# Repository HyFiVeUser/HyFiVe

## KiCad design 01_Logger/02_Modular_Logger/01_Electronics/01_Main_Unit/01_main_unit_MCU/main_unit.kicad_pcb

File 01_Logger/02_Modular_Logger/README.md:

# Assembly Instructions

## 1. Battery and Wi-Fi Antenna

1. Place the battery into the battery holder.
2. Attach the Wi-Fi antenna.

<table>
  <tr>
    <td></td>
    <td></td>
    <td></td>
    <td></td>
  </tr>
</table>

## 2. Measurement Sensors

Attach the measurement sensors.

## 3. Mainboard and Interface Board

1. Connect the mainboard to the interface board.
2. Ensure the correct polarity of the connector.

<table>
  <tr>
    <td></td>
    <td></td>
    <td></td>
  </tr>
</table>

## 4. Screw Components and Connect Plugs

1. Screw the parts together.
2. Plug in both NTC connectors.
3. Plug in the LED and reed switch connectors.
4. Connect the charging plug.

<table>
  <tr>
    <td></td>
    <td></td>
    <td></td>
  </tr>
</table>

## 5. LED and Reed Switch

1. Attach the LED and reed switch.
2. Secure them with hot glue.

## 6. Configure SD Card

Configure the SD card with the file `loggerConfig/logger_XX_config_2024XXXXXXXX.json`. Pay attention to the following points:

1. **Filename**: 
   - Replace "XX" in the filename with the correct logger number and date in the format year/month/day/hour/minute.
   - Example: For logger 13, the filename would be `logger_13_config_202409131028.json`

2. **Logger ID**:
   - In the configuration file, the "logger_id" field must contain the correct logger number.
   - Example: `"logger_id": "13"`

3. **Wi-Fi Setup**:
   - Configure the Wi-Fi settings.
   - The first Wi-Fi login should be for the corresponding deck box.
   - You can configure up to 5 different Wi-Fi networks.

Example for Wi-Fi configuration:

```json
"wifi": [
  {
    "ssid": "Deckbox_SSID",
    "password": "Deckbox_Password"
  },
  {
    "ssid": "Second_WiFi",
    "password": "Second_Password"
  }
]
```

## 7. Connect Battery and Start Device

1. Connect the battery voltage to the mainboard.
2. Press the Boot-BMS button.
3. The board starts and can be assembled.
4. Leak test still needs to be carried out

<table>
  <tr>
    <td></td>
    <td></td>
    <td></td>
  </tr>
</table>

## 8. Vacuum Leak Test

The following tools are required to perform the vacuum leak test:

Mityvac Hand Operated Vacuum Pump
https://bluerobotics.com/store/watertight-enclosures/enclosure-tools-supplies/vacuum-pump-kit-r2-rp/

Vacuum Plug
https://bluerobotics.com/store/watertight-enclosures/enclosure-tools-supplies/vacuum-plug/

Pressure Relief Valve Backfill Adapter
https://bluerobotics.com/store/watertight-enclosures/prv-m10-backfill-adapter/

After completing the assembly, a vacuum leak test must be performed to verify the watertight integrity of the enclosure.

1. Connect the vacuum pump to the enclosure using the appropriate adapter.

2. The target vacuum level is 30 inHg VAC (approx. 1 bar pressure differential).

3. Monitor the achieved vacuum level for approximately 24 hours.

4. If the vacuum remains stable within the permissible tolerance, the leak test is considered successful.

## 9. Battery Pack Assembly (4S3P)

The logger battery pack consists of 12 Sony/Murata US18650VTC6 cells in a 4S3P configuration.

> **Safety:** Lithium-ion cells can cause fire or serious injury if short-circuited, damaged, incorrectly connected, or overheated. Pack assembly and spot welding must only be performed by a trained person with suitable equipment and fire-safety measures.

### Materials and tools

| Qty. | Description |
|---:|---|
| 1 | Spot welder suitable for battery cells (listed peak current: at least 650 A) |
| 5 | 5-pin connector housing, Molex 43645-0500 |
| 5 | Crimp contacts, AWG 24–20, Molex 43030-0003 |
| 1 | Black hook-up wire, 1.0 mm² |
| 1 | Red hook-up wire, 1.0 mm² |
| 3 | Blue hook-up wire, 0.25 mm² |
| 2 | 10 kΩ NTC thermistors, 103AT-2 |
| 1 | Heat-shrink tubing, Ø95.5 mm × 1 m, 2:1 shrink ratio |
| 1 | Nickel strip, 0.15 mm × 10 m |
| 12 | Li-ion cells, US18650VTC6 |

### Assembly

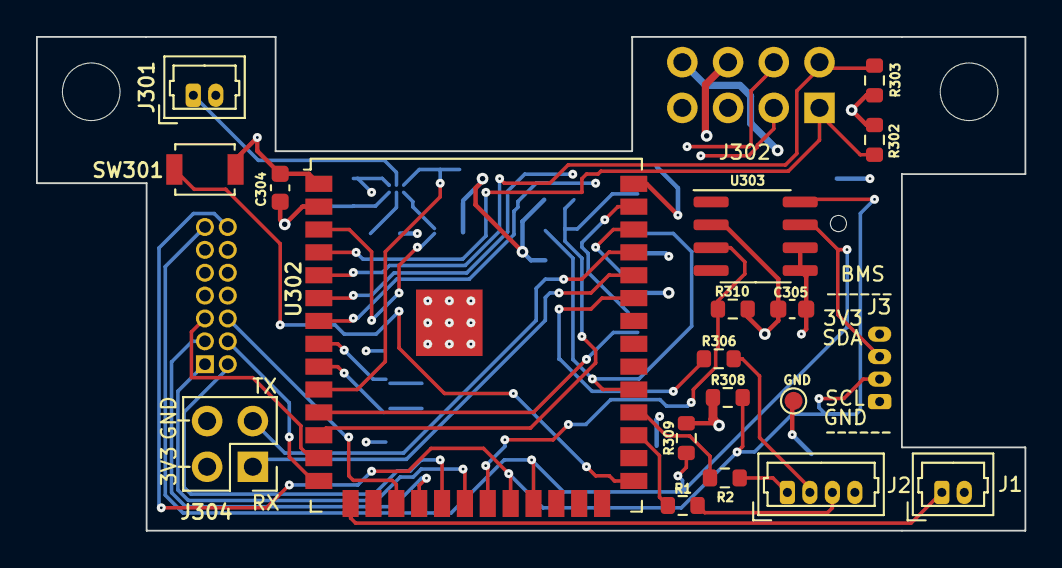
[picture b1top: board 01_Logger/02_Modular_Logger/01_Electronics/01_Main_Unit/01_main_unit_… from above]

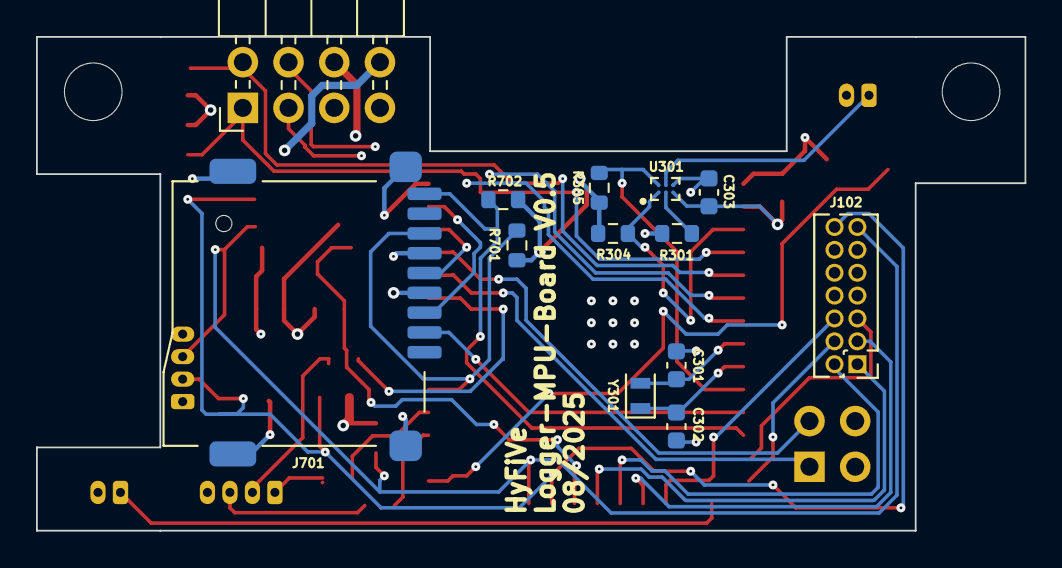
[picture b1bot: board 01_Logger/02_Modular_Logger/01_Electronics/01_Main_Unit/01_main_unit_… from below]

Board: 4 copper layers, 54.9 x 27.4 mm, 34 parts (13 on the bottom side), 35 nets.

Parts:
C301, C302: 20pF; C_0603_1608Metric
C303, C304, C305: 100nF 50V; C_0603_1608Metric
H303, H305: MountingHole; MountingHole_3.2mm_M3_ISO7380
J1, J301: Conn_01x02; Molex_PicoBlade_53047-0210_1x02_P1.25mm_Vertical
J2, J3: Conn_01x04_Pin; Molex_PicoBlade_53047-0410_1x04_P1.25mm_Vertical
J102: FTS-107-01-F-D; PinHeader_2x07_P1.27mm_Vertical
J302: Conn_02x04_Counter_Clockwise; PinHeader_2x04_P2.54mm_Horizontal
J304: Conn_02x02_Odd_Even; PinHeader_2x02_P2.54mm_Vertical
J701: Micro_SD_Card_Det; SD_CARD_693071020811
R1, R2: 0R; R_0603_1608Metric
R301: 470k; R_0603_1608Metric
R302, R303, R304, R305, R308, R309, R310, R701, R702: 10k; R_0603_1608Metric
R306: 68R; R_0603_1608Metric
SW301: SW_Push; SW_SPST_B3U-1000P
TP303: TestPoint; TestPoint_Pad_D1.0mm
U301: MAX16125WTEG00+T; WLP-6
U302: ESP32-S3-WROOM-1U
U303: DS3231MZ; SOIC-8_3.9x4.9mm_P1.27mm
Y301: Crystal; Crystal_SMD_TXC_9HT11-2Pin_2.0x1.2mm

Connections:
+3V3: C303.1, C304.1, C305.1, J3.4, J102.10, J302.8, J304.2, J701.4 (VDD), R302.1, R303.1, R304.1, R305.1, R308.1, R309.1, R310.1, R701.2, R702.1, U301.C1 (VCC), U302.2 (VDD), U303.2 (VCC)
+5V: J102.11, J302.7
+12V: J102.12, J302.6
/MPU/Charge_Enable: J102.3, U302.18 (IO10)
/MPU/ENABLE_5V: J102.1, U302.20 (IO12)
/MPU/ENABLE_12V: J102.2, U302.19 (IO11)
/MPU/GPIO_Reserve_B2B: J302.4, U302.6 (IO6)
/MPU/I2C_BUS_CLK: J302.2, R303.2, U302.5 (IO5)
/MPU/I2C_BUS_SDA: J302.1, R302.2, U302.4 (IO4)
/MPU/I2C_SMBus_SCL: J3.2, J102.14, R308.2, U302.22 (IO14), U303.8 (SCL)
/MPU/I2C_SMBus_SDA: J3.3, J102.13, R309.2, U302.23 (IO21), U303.7 (SDA)
/MPU/Interface_RST: J302.3, U302.7 (IO7)
/MPU/LED_ROT: R306.1, U302.35 (IO42)
/MPU/RST: R304.2, U301.A1 (/RESET), U302.3 (EN)
/MPU/RTC_INTERRUPT: R310.2, U302.21 (IO13), U303.3 (~INT/SQW)
/MPU/SD_CARD_DETECT: J701.9 (DET_B), R702.2, U302.12 (IO8)
/MPU/SD_V_SPI_CLK: J701.5 (CLK), U302.38 (IO2)
/MPU/SD_V_SPI_CS: J701.2 (DAT3/CD), U302.11 (IO18)
/MPU/SD_V_SPI_MISO: J701.7 (DAT0), R701.1, U302.31 (IO38)
/MPU/SD_V_SPI_MOSI: J701.3 (CMD), U302.39 (IO1)
/MPU/UART_RXD0: J304.1, U302.36 (RXD0)
/MPU/UART_TXD0: J304.3, U302.37 (TXD0)
/MPU/~PG: J102.4, U302.14 (IO20)
/MPU/~STAT1: J102.6, U302.17 (IO9)
/MPU/~STAT2: J102.5, U302.13 (IO19)
GND: C301.2, C302.2, C303.2, C304.2, C305.2, J1.2, J2.4, J3.1, J102.7, J102.8, J301.2, J302.5, J304.4, J701.6 (VSS), J701.10 (DET_A), J701.11 (SHIELD), J701.12 (SHIELD), J701.13 (SHIELD), R301.2, SW301.2, TP303.1, U301.C2 (GND), U302.1 (GND), U302.40 (GND), U302.EPAD (GND), U303.5 (GND), U303.6 (VBAT)
unnamed: J2.1, R2.1
unnamed: J2.2, R306.2
unnamed: J2.3, R1.1
unnamed: J301.1, U301.B2 (/MR)
unnamed: R301.1, U301.B1 (SEL)
unnamed: R305.2, U301.A2 (/SRESET), U302.10 (IO17)
unnamed: SW301.1, U302.27 (IO0)
unnamed: C301.1, U302.8 (IO15), Y301.2
unnamed: C302.1, U302.9 (IO16), Y301.1

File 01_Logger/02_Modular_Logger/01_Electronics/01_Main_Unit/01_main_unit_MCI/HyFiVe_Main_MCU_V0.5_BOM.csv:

"Reference","Value","Datasheet","Footprint","Qty","DNP","eurocircuits_MPN"
"C301,C302","20pF","~","Capacitor_SMD:C_0603_1608Metric","2","","CL10C200JB8NNNC"
"C303,C304,C305","100nF 50V","~","Capacitor_SMD:C_0603_1608Metric","3","","885012206095"
"FID301,FID302,FID303,FID304","Fiducial","~","Sonstiges:Passmarke","4","",""
"H303,H305","MountingHole","~","MountingHole:MountingHole_3.2mm_M3_ISO7380","2","",""
"J1","Conn_01x02","~","Connector_Molex:Molex_PicoBlade_53047-0210_1x02_P1.25mm_Vertical","1","Nicht bestücken","53047-0210"
"J2","Conn_01x04_Pin","~","Connector_Molex:Molex_PicoBlade_53047-0410_1x04_P1.25mm_Vertical","1","","53047-0410"
"J3","Conn_01x04_Pin","~","Connector_Molex:Molex_PicoBlade_53047-0410_1x04_P1.25mm_Vertical","1","Nicht bestücken","53047-0410"
"J102","FTS-107-01-F-D","https://www.mouser.de/datasheet/2/527/fts-2854063.pdf","Connector_PinHeader_1.27mm:PinHeader_2x07_P1.27mm_Vertical","1","","FTS-107-01-F-D"
"J301","Conn_01x02","~","Connector_Molex:Molex_PicoBlade_53047-0210_1x02_P1.25mm_Vertical","1","","53047-0210"
"J302","Conn_02x04_Counter_Clockwise","~","Connector_PinHeader_2.54mm:PinHeader_2x04_P2.54mm_Horizontal","1","Nicht bestücken",""
"J304","Conn_02x02_Odd_Even","~","Connector_PinHeader_2.54mm:PinHeader_2x02_P2.54mm_Vertical","1","","61300421121"
"J701","Micro_SD_Card_Det","https://www.hirose.com/product/en/download_file/key_name/DM3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","HER_Footprints:SD_CARD_693071020811","1","","693071020811"
"R1,R2","0R","~","Resistor_SMD:R_0603_1608Metric","2","","GPR06030R"
"R301","470k","~","Resistor_SMD:R_0603_1608Metric","1","","GPR0603470K"
"R302,R303,R304,R305,R308,R309,R310,R701,R702","10k","~","Resistor_SMD:R_0603_1608Metric","9","","MCWR06X1002FTL"
"R306","68R","~","Resistor_SMD:R_0603_1608Metric","1","","GPR060368R"
"SW301","SW_Push","~","Button_Switch_SMD:SW_SPST_B3U-1000P","1","","B3U-1000P"
"TP303","TestPoint","~","TestPoint:TestPoint_Pad_D1.0mm","1","",""
"U301","MAX16125WTEG00+T","","MAX6071ANT25_T:WLP-6","1","","MAX16125WTEG00+T"
"U302","ESP32-S3-WROOM-1U","https://www.espressif.com/sites/default/files/documentation/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","HER_Footprints:ESP32-S3-WROOM-1U","1","","ESP32-S3-WROOM-1U-N16R8"
"U303","DS3231MZ","http://datasheets.maximintegrated.com/en/ds/DS3231M.pdf","Package_SO:SOIC-8_3.9x4.9mm_P1.27mm","1","","DS3231MZ+"
"Y301","Crystal","~","Crystal:Crystal_SMD_TXC_9HT11-2Pin_2.0x1.2mm","1","","9HT11-32.768KDZF-T "

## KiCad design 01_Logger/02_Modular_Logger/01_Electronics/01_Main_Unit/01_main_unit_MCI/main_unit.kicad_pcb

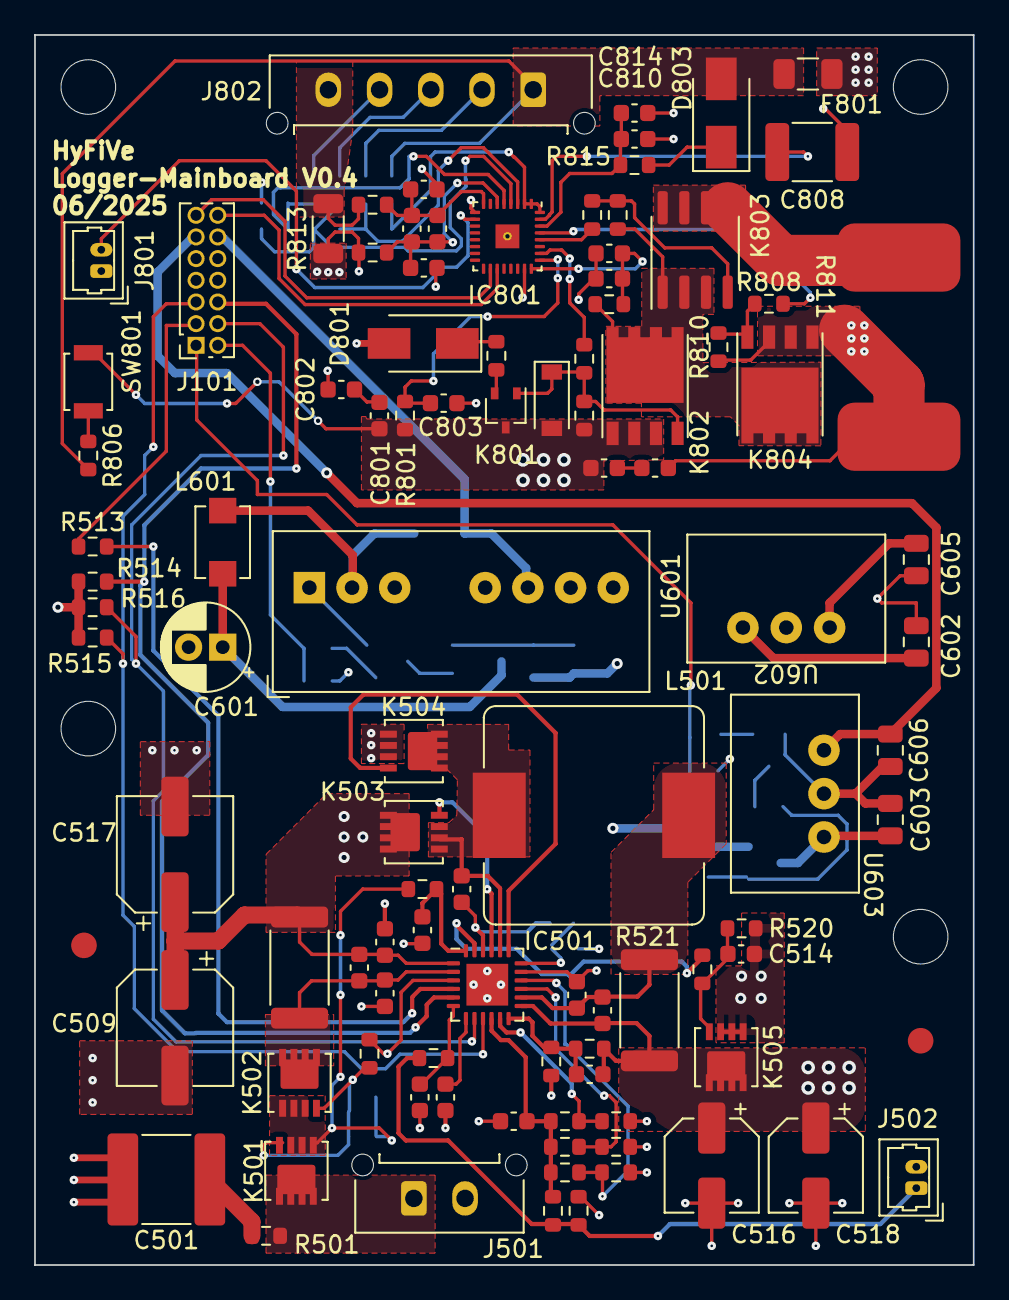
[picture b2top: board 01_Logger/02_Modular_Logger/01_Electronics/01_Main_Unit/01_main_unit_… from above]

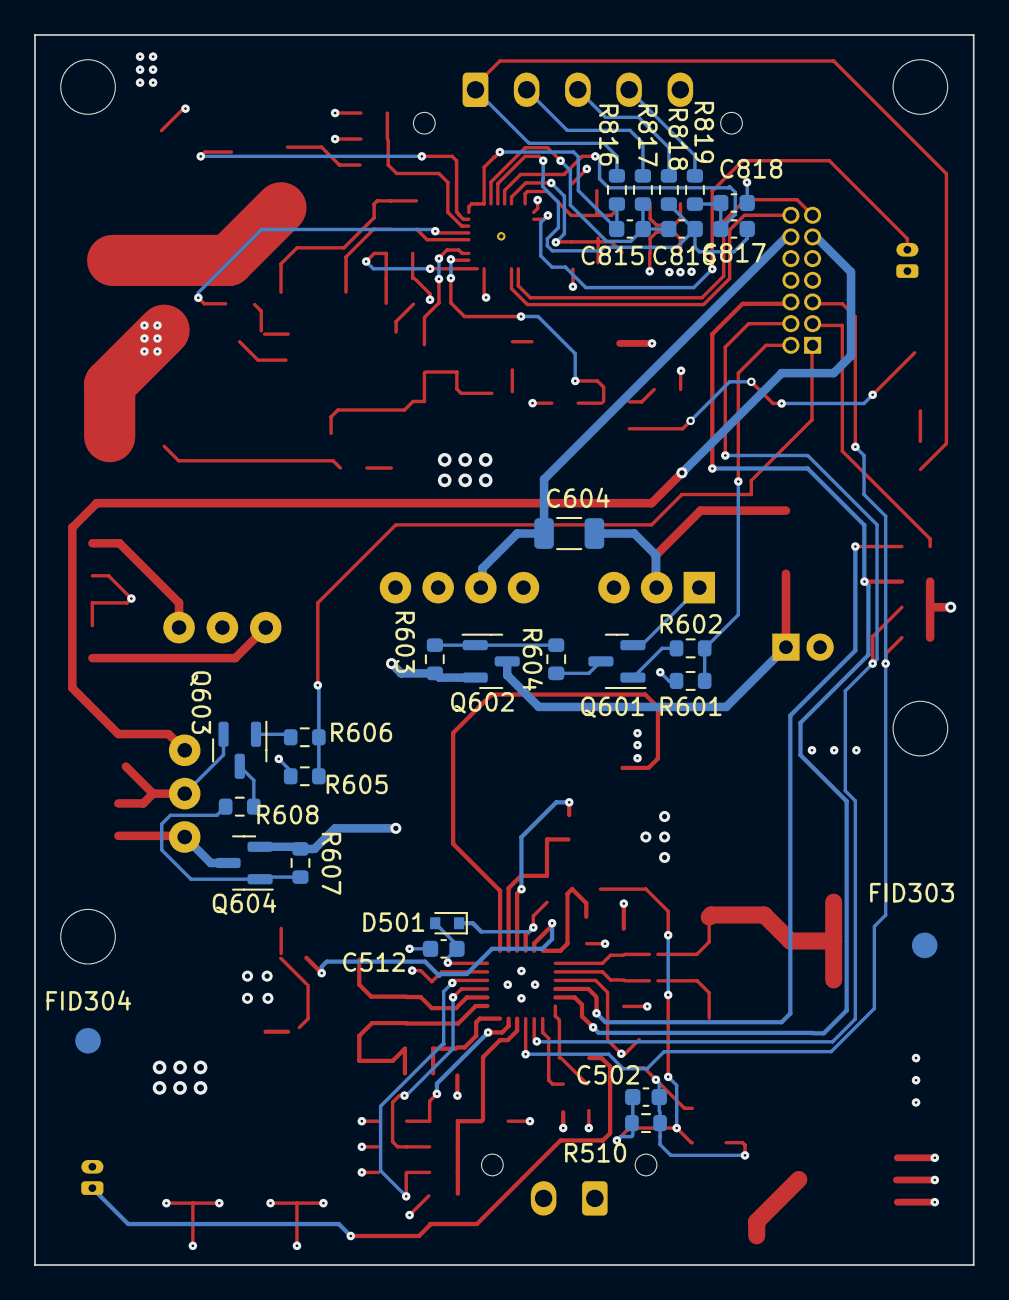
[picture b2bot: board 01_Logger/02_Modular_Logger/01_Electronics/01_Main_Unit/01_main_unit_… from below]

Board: 4 copper layers, 55.0 x 72.1 mm, 132 parts (27 on the bottom side), 78 nets.

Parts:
C501: 47µF 35V X7R; C_2220_5650Metric
C502, C503, C505, C506, C507, C511, C513, C514, C515, C801, C802, C806, C807, C809, C812, C813, C815, C816, C817, C818: 100nF 50V; C_0603_1608Metric
C504: 1µF 10V; C_0603_1608Metric
C508: 33nF 25V; C_0603_1608Metric
C509, C517: 47µF 35V; CP_Elec_6.3x5.4
C510, C512: 1µF 35V; C_0603_1608Metric
C516, C518: 20µF 35V; CP_Elec_5x5.3
C519: 22pF 35V; C_0603_1608Metric
C601: 10µF, 50V; CP_Radial_D5.0mm_P2.00mm
C602, C603: 22µF 30V; C_0805_2012Metric
C604: 150pF, 2kV; C_1206_3216Metric
C605, C606: 47µF 10V; C_0805_2012Metric
C803: 10nF, 50V; C_0603_1608Metric
C804, C805, C810, C814: 100pF 50V; C_0603_1608Metric
C808: 2,2µF 100V; C_1812_4532Metric
C811: 100pF 100V; C_0603_1608Metric
D501: BAT54W; D_SOD-523
D801, D803: SS1H10-E3/61T; D_SMA
D802: MMSZ5246B-7-F; D_SOD-123
F801: 12A; Fuse_1206_3216Metric
FID301, FID302, FID303, FID304: Fiducial; Passmarke
H301, H302, H304, H306: MountingHole; MountingHole_3.2mm_M3_ISO7380
IC501: BQ24618; VQFN-24-1EP_4x4mm_P0.5mm_EP2.45x2.45mm
IC801: BQ40Z80; RSM32 VQFN-32-1EP_4x4mm_P0.4mm_EP1.4x1.4mm_ThermalVias
J101: SFMC-107-01-L-D; PinSocket_2x07_P1.27mm_Vertical
J501: Conn_01x02; Molex_Micro-Fit_3.0_43650-0215_1x02_P3.00mm_Vertical
J502: Conn_01x02_Female; Molex_PicoBlade_53047-0210_1x02_P1.25mm_Vertical
J801: Conn_01x02_Male; Molex_PicoBlade_53047-0210_1x02_P1.25mm_Vertical
J802: Conn_01x05_Male; Molex_Micro-Fit_3.0_43650-0515_1x05_P3.00mm_Vertical
K501, K502, K505: SISH101DN-T1-GE3; PowerPAK 1212-8 Single
K503, K504: SiS412DN; PowerPAK 1212-8 Single
K801: 2N7002KW; SOT-323_SC-70
K802, K804: CSD18540Q5B; TI Q5B-Package
K803: DMP6023LSS-13; SOIC-8_3.9x4.9mm_P1.27mm
L501: 3,3µH; L_Bourns_SRP1245A
L601: 10µH; CC453232A
Q601, Q603: BSS123; SOT-23
Q602, Q604: IRLML5203TRPBF; SOT-23
R501, R511, R812, R814, R815: 100R; R_0603_1608Metric
R502, R507, R802, R809: 10k; R_0603_1608Metric
R503: 5.7k; R_0603_1608Metric
R504: R_Therm_1; R_0603_1608Metric
R505: R_Therm_2; R_0603_1608Metric
R506, R510, R520: 100k; R_0603_1608Metric
R508: 232k; R_0603_1608Metric
R509: 33k; R_0603_1608Metric
R512, R519, R604, R608, R808: 1k; R_0603_1608Metric
R513: 0R; R_0603_1608Metric
R514, R515, R516, R523: 49,9k; R_0603_1608Metric
R517, R521: 10m; R_2512_6332Metric
R518: 10R; R_0603_1608Metric
R522: 357k; R_0603_1608Metric
R601, R605: 2k7; R_0603_1608Metric
R602, R606: 47k; R_0603_1608Metric
R603, R607: 680k; R_0603_1608Metric
R801: 1,1k; R_0603_1608Metric
R803, R807, R810: 10M; R_0603_1608Metric
R804: 4,81k; R_0603_1608Metric
R805: 510R; R_0603_1608Metric
R806: 51R; R_0603_1608Metric
R811: 46.4 5W; R_4527_11570Metric
R813: 1m; R_1206_3216Metric
R816, R817, R818, R819: 499R; R_0603_1608Metric
SW801: SW_Push; SW_SPST_B3U-1000P
U601: SPBW06F-12; Converter_DCDC_XP_POWER-ITxxxxxS_THT
U602: OKI-78SR-3.3_1.5-W36-C; DC_DC_Converter
U603: OKI-78SR-5_1.5-W36-C; DC_DC_Converter

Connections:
+3V3: C605.1, J101.10, R514.1, R515.1, R516.1, U602.3 (OUT)
+5V: C606.1, J101.11, U603.3 (OUT)
+12V: C604.2, J101.12, U601.6 (+VOUT)
/power/BMS/BAT_MINUS: J802.5, R813.2, R814.1
/power/BMS/BAT_PLUS: D803.2 (A), F801.2, J802.1, R806.2, R816.1
/power/BMS/BAT_PLUS_F: C807.1, F801.1, K804.1, K804.2, K804.3, R810.2, R811.2
/power/BMS/PACK+: C515.1, C516.1, C518.1, C519.2, C801.1, C806.1, D802.2 (A), IC501.13 (SRN), K505.5, K505.6, K505.7, K505.8, K505.9, K801.3, K802.1, K802.2, K802.3, R521.1, R522.1, R801.2, R803.2, SW801.2
/power/Battery_Charger/ACP: C503.2, C505.1, IC501.2 (ACP), K502.5, K502.6, K502.7, K502.8, K502.9, R517.2
/power/Battery_Charger/Thermistor: J502.1, R504.1, R505.2, R511.1
/power/Battery_Charger/VIN: J501.1, K501.5, K501.6, K501.7, K501.8, K501.9, R501.1
/power/Battery_Charger/VREF: C504.1, IC501.10 (VREF), R502.1, R504.2, R506.1, R508.1
/power/Charge_Enable: J101.3, R513.1
/power/ENABLE_5V: J101.1, R605.2, R606.1
/power/ENABLE_12V: J101.2, R601.2, R602.1
/power/I2C_SMBus_SCL: IC801.19 (SMBC), J101.14
/power/I2C_SMBus_SDA: IC801.18 (SMBD), J101.13
/power/System+: C505.2, C507.2, C509.1, C514.1, C517.1, C602.1, IC501.1 (ACN), K503.5, K503.6, K503.7, K503.8, K503.9, K505.1, K505.2 (S), K505.3 (S), Q602.2 (S), Q604.2 (S), R517.1, R520.1, R603.2, R607.2, U602.1 (IN)
/power/~PG: IC501.8 (~PG), J101.4, R516.2
/power/~STAT1: IC501.5 (~STAT1), J101.6, R514.2
/power/~STAT2: IC501.9 (~STAT2), J101.5, R515.2
GND: C501.2, C503.1, C504.2, C506.1, C507.1, C508.1, C509.2, C510.2, C512.2, C513.1, C516.2, C517.2, C518.2, C601.2, C602.2, C603.2, C605.2, C606.2, C802.2, C803.2, C804.1, C805.1, C808.2, C809.1, C810.1, C813.1, C814.1, C818.2, D801.2 (A), IC501.17 (GND), IC501.25 (PwrPad), IC801.9 (VSS), IC801.23 (FUSE), IC801.33 (PAD), J101.7, J101.8, J501.2, J502.2, J801.1, K504.1, K504.2 (S), K504.3 (S), Q601.2 (S), Q603.2 (S), R503.2, R505.1, R507.2, R509.2, R523.2, R601.1, R605.1, R812.2, R813.1, U601.1 (-VIN), U601.7 (-VOUT), U602.2 (GND), U603.2 (GND)
unnamed: C501.1, R501.2
unnamed: C502.1, K501.1, K501.2 (S), K501.3 (S), K502.1, K502.2 (S), K502.3 (S), R510.1, R518.2
unnamed: C502.2, K501.4, K502.4, R510.2, R512.1
unnamed: C514.2, K505.4, R519.1, R520.2
unnamed: C801.2, C802.1
unnamed: C806.2, C807.2
unnamed: C512.1, D501.2 (A), IC501.18 (REGN)
unnamed: C511.1, D501.1 (K), IC501.22 (BTST)
unnamed: D801.1 (K), R802.1
unnamed: D802.1 (K), K801.1, K802.4, R803.1, R804.2
unnamed: D803.1 (K), R815.1
unnamed: IC501.16 (ACSET), R502.2, R503.1
unnamed: IC501.4 (CE), R513.2
unnamed: IC501.21 (HIDRV), K503.4
unnamed: IC501.11 (ISET1), R508.2, R509.1
unnamed: IC501.15 (ISET2), R506.2, R507.1
unnamed: IC501.19 (LODRV), K504.4
unnamed: C511.2, IC501.20 (PH), K503.1, K503.2 (S), K503.3 (S), K504.5, K504.6, K504.7, K504.8, K504.9, L501.1
unnamed: C513.2, C515.2, IC501.14 (SRP), L501.2, R521.2
unnamed: C506.2, IC501.6 (TS), R511.2
unnamed: C508.2, IC501.7 (TTC)
unnamed: C510.1, IC501.24 (VCC), R518.1
unnamed: C519.1, IC501.12 (VFB), R522.2, R523.1
unnamed: IC501.3 (~ACDRV), R512.2
unnamed: IC501.23 (~BATDRV), R519.2
unnamed: C810.2, C814.2, IC801.30 (BAT), R815.2
unnamed: IC801.29 (CHG), R808.1
unnamed: IC801.26 (DSG), R804.1
unnamed: C808.1, IC801.31 (PBI)
unnamed: IC801.28 (PCHG), R809.1
unnamed: C803.1, IC801.25 (Pack), R801.1
unnamed: C809.2, C811.2, C812.2, IC801.6 (SRN), R812.1
unnamed: C811.1, C812.1, C813.2, IC801.8 (SRP), R814.2
unnamed: IC801.10 (TS1), J801.2
unnamed: C817.2, C818.1, IC801.5 (VC1), R819.2
unnamed: C816.2, C817.1, IC801.4 (VC2), R818.2
unnamed: C815.2, C816.1, IC801.3 (VC3), R817.2
unnamed: C815.1, IC801.1 (VC5), IC801.2 (VC4), IC801.32 (VC6), R816.2
unnamed: C804.2, C805.2, IC801.24 (VCC), R805.1
unnamed: J802.2, R817.1
unnamed: J802.3, R818.1
unnamed: J802.4, R819.1
unnamed: K801.2, R802.2
unnamed: K802.5, K802.6, K802.7, K802.8, K802.9, K803.1, K803.2, K803.3, K804.5, K804.6, K804.7, K804.8, K804.9, R805.2, R807.2
unnamed: K803.4, R807.1, R809.2
unnamed: K803.5, K803.6, K803.7, K803.8, R811.1
unnamed: K804.4, R808.2, R810.1
unnamed: Q601.3 (D), R604.1
unnamed: Q601.1 (G), R602.2
unnamed: C601.1, L601.1, Q602.3 (D)
unnamed: Q602.1 (G), R603.1, R604.2
unnamed: Q603.3 (D), R608.1
unnamed: Q603.1 (G), R606.2
unnamed: C603.1, Q604.3 (D), U603.1 (IN)
unnamed: Q604.1 (G), R607.1, R608.2
unnamed: R806.1, SW801.1
unnamed: C604.1, L601.2, U601.2 (+VIN)

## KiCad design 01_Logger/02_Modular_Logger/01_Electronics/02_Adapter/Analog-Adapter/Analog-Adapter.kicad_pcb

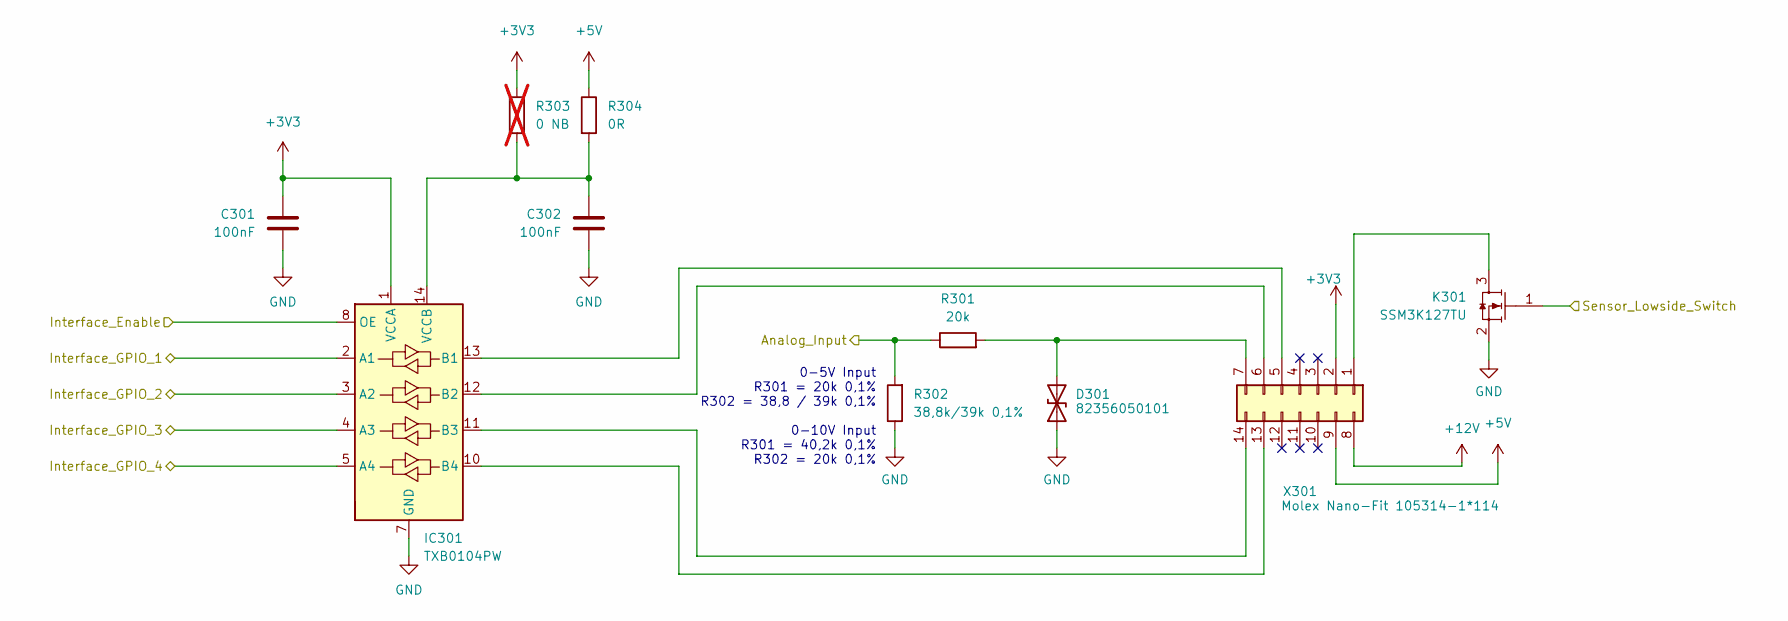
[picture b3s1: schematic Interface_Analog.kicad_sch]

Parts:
C301, C302: 100nF; C_0603_1608Metric_Pad1.08x0.95mm_HandSolder
D301: 82356050101; D_0603_1608Metric
IC301: TXB0104PW; TSSOP-14_4.4x5mm_P0.65mm
K301: SSM3K127TU; SOT-23
R301: 20k; R_0603_1608Metric_Pad0.98x0.95mm_HandSolder
R302: 38,8k/39k 0,1%; R_0603_1608Metric_Pad0.98x0.95mm_HandSolder
R303: 0 NB; R_0603_1608Metric_Pad0.98x0.95mm_HandSolder; not fitted
R304: 0R; R_0603_1608Metric_Pad0.98x0.95mm_HandSolder
X301: Molex Nano-Fit 105314-1*114; Molex_Nano-Fit_105314-xx14_2x07_P2.50mm_Horizontal

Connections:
+3V3: C301.1, IC301.1 (VCCA), R303.1, X301.2; also elsewhere on the board
+5V: R304.1, X301.9; also elsewhere on the board
+12V: X301.8; also elsewhere on the board
/MCU/Interface_Analog: R301.1, R302.2; also elsewhere on the board
/MCU/Interface_Enable: IC301.8 (OE); also elsewhere on the board
/MCU/Interface_GPIO_1: IC301.2 (A1); also elsewhere on the board
/MCU/Interface_GPIO_2: IC301.3 (A2); also elsewhere on the board
/MCU/Interface_GPIO_3: IC301.4 (A3); also elsewhere on the board
/MCU/Interface_GPIO_4: IC301.5 (A4); also elsewhere on the board
/MCU/Sensor_Lowside_Switch: K301.1; also elsewhere on the board
GND: C301.2, C302.2, D301.1 (A1), IC301.7 (GND), K301.2, R302.1; also elsewhere on the board
unnamed: D301.2 (A2), R301.2, X301.7
unnamed: IC301.13 (B1), X301.5
unnamed: IC301.12 (B2), X301.6
unnamed: IC301.11 (B3), X301.14
unnamed: IC301.10 (B4), X301.13
unnamed: C302.1, IC301.14 (VCCB), R303.2, R304.2
unnamed: K301.3, X301.1

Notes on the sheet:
0-5V Input R301 = 20k 0,1% R302 = 38,8 / 39k 0,1% 0-10V Input R301 = 40,2k 0,1% R302 = 20k 0,1%

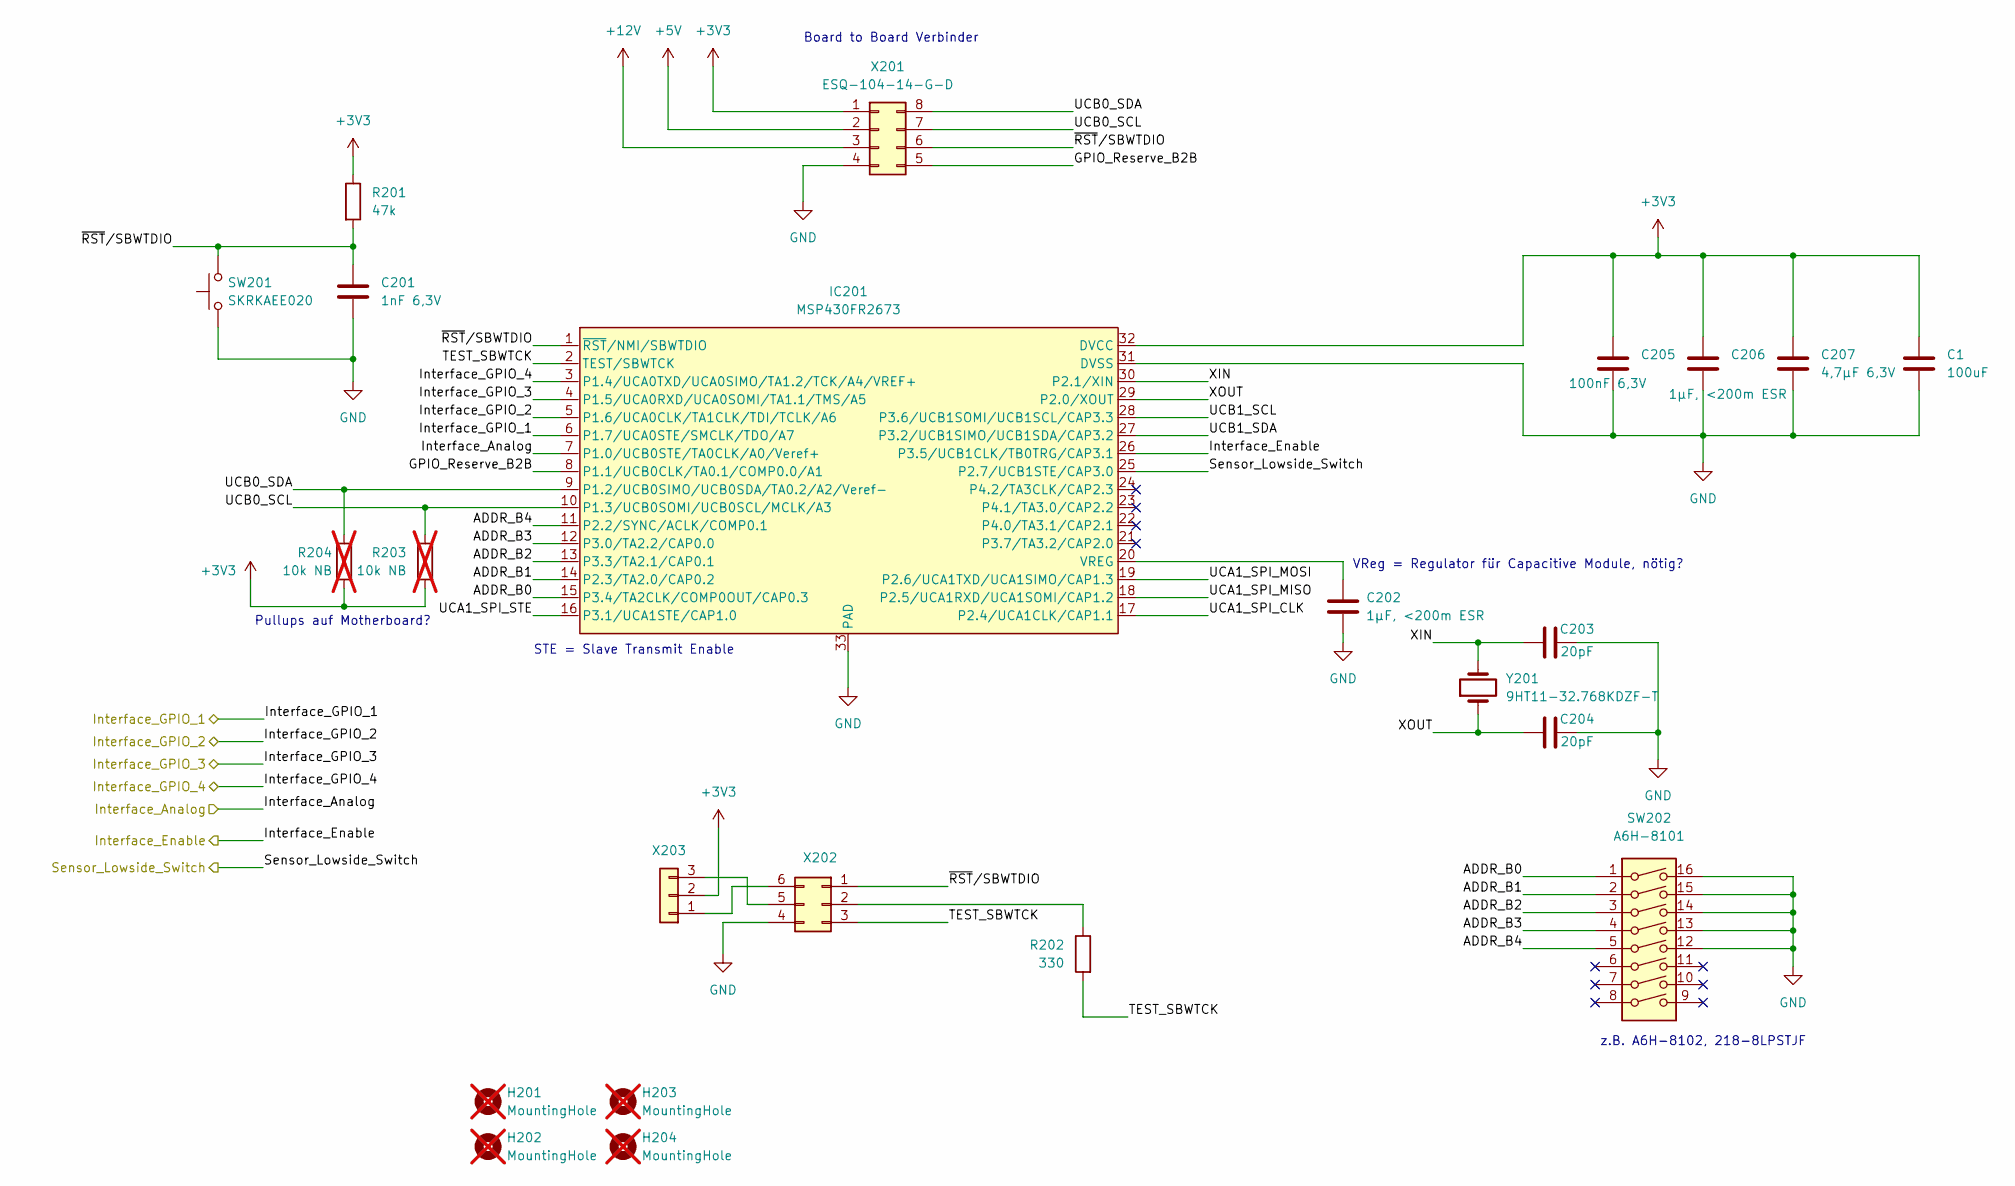
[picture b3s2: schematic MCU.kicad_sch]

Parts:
C1: 100uF; C_0805_2012Metric_Pad1.18x1.45mm_HandSolder
C201: 1nF 6,3V; C_0603_1608Metric_Pad1.08x0.95mm_HandSolder
C202, C206: 1µF, <200m ESR; C_0603_1608Metric_Pad1.08x0.95mm_HandSolder
C203, C204: 20pF; C_0603_1608Metric_Pad1.08x0.95mm_HandSolder
C205: 100nF 6,3V; C_0603_1608Metric_Pad1.08x0.95mm_HandSolder
C207: 4,7µF 6,3V; C_0603_1608Metric_Pad1.08x0.95mm_HandSolder
H201, H202, H203, H204: MountingHole; MountingHole_2.7mm_M2.5; not fitted
IC201: MSP430FR2673; VQFN-32-1EP_5x5mm_P0.5mm_EP3.5x3.5mm
R201: 47k; R_0603_1608Metric_Pad0.98x0.95mm_HandSolder
R202: 330; R_0603_1608Metric_Pad0.98x0.95mm_HandSolder
R203, R204: 10k NB; R_0603_1608Metric_Pad0.98x0.95mm_HandSolder; not fitted
SW201: SKRKAEE020; SW_Push_SPST_NO_Alps_SKRK
SW202: A6H-8101; SW_DIP_SPSTx08_Slide_Omron_A6H-8101_W6.15mm_P1.27mm
X201: ESQ-104-14-G-D; PinSocket_2x04_P2.54mm_Vertical
X202: Conn_02x03_Counter_Clockwise; PinHeader_2x03_P2.54mm_Vertical
X203: Conn_01x03; PinHeader_1x03_P2.54mm_Vertical
Y201: 9HT11-32.768KDZF-T; Crystal_SMD_TXC_9HT11-2Pin_2.0x1.2mm_HandSoldering

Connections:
+3V3: C1.1, C205.1, C206.1, C207.1, IC201.32 (DVCC), R201.1, R203.2, R204.2, X201.1, X203.2; also elsewhere on the board
+5V: X201.2; also elsewhere on the board
+12V: X201.3; also elsewhere on the board
/MCU/ADDR_B0: IC201.15 (P3.4/TA2CLK/COMP0OUT/CAP0.3), SW202.1
/MCU/ADDR_B1: IC201.14 (P2.3/TA2.0/CAP0.2), SW202.2
/MCU/ADDR_B2: IC201.13 (P3.3/TA2.1/CAP0.1), SW202.3
/MCU/ADDR_B3: IC201.12 (P3.0/TA2.2/CAP0.0), SW202.4
/MCU/ADDR_B4: IC201.11 (P2.2/SYNC/ACLK/COMP0.1), SW202.5
/MCU/GPIO_Reserve_B2B: IC201.8 (P1.1/UCB0CLK/TA0.1/COMP0.0/A1), X201.5
/MCU/Interface_Analog: IC201.7 (P1.0/UCB0STE/TA0CLK/A0/Veref+); also elsewhere on the board
/MCU/Interface_Enable: IC201.26 (P3.5/UCB1CLK/TB0TRG/CAP3.1); also elsewhere on the board
/MCU/Interface_GPIO_1: IC201.6 (P1.7/UCA0STE/SMCLK/TDO/A7); also elsewhere on the board
/MCU/Interface_GPIO_2: IC201.5 (P1.6/UCA0CLK/TA1CLK/TDI/TCLK/A6); also elsewhere on the board
/MCU/Interface_GPIO_3: IC201.4 (P1.5/UCA0RXD/UCA0SOMI/TA1.1/TMS/A5); also elsewhere on the board
/MCU/Interface_GPIO_4: IC201.3 (P1.4/UCA0TXD/UCA0SIMO/TA1.2/TCK/A4/VREF+); also elsewhere on the board
/MCU/Sensor_Lowside_Switch: IC201.25 (P2.7/UCB1STE/CAP3.0); also elsewhere on the board
/MCU/TEST_SBWTCK: IC201.2 (TEST/SBWTCK), R202.2, X202.3
/MCU/UCA1_SPI_CLK: IC201.17 (P2.4/UCA1CLK/CAP1.1)
/MCU/UCA1_SPI_MISO: IC201.18 (P2.5/UCA1RXD/UCA1SOMI/CAP1.2)
/MCU/UCA1_SPI_MOSI: IC201.19 (P2.6/UCA1TXD/UCA1SIMO/CAP1.3)
/MCU/UCA1_SPI_STE: IC201.16 (P3.1/UCA1STE/CAP1.0)
/MCU/UCB0_SCL: IC201.10 (P1.3/UCB0SOMI/UCB0SCL/MCLK/A3), R203.1, X201.7
/MCU/UCB0_SDA: IC201.9 (P1.2/UCB0SIMO/UCB0SDA/TA0.2/A2/Veref-), R204.1, X201.8
/MCU/UCB1_SCL: IC201.28 (P3.6/UCB1SOMI/UCB1SCL/CAP3.3)
/MCU/UCB1_SDA: IC201.27 (P3.2/UCB1SIMO/UCB1SDA/CAP3.2)
/MCU/XIN: C203.1, IC201.30 (P2.1/XIN), Y201.2
/MCU/XOUT: C204.1, IC201.29 (P2.0/XOUT), Y201.1
/MCU/~RST/SBWTDIO: C201.1, IC201.1 (~RST/NMI/SBWTDIO), R201.2, SW201.2, X201.6, X202.1
GND: C1.2, C201.2, C202.2, C203.2, C204.2, C205.2, C206.2, C207.2, IC201.31 (DVSS), IC201.33 (PAD), SW201.1, SW202.12, SW202.13, SW202.14, SW202.15, SW202.16, X201.4, X202.4; also elsewhere on the board
unnamed: C202.1, IC201.20 (VREG)
unnamed: R202.1, X202.2
unnamed: X202.5, X203.3
unnamed: X202.6, X203.1

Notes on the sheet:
STE = Slave Transmit Enable
Pullups auf Motherboard?
Board to Board Verbinder
z.B. A6H-8102, 218-8LPSTJF
VReg = Regulator für Capacitive Module, nötig?

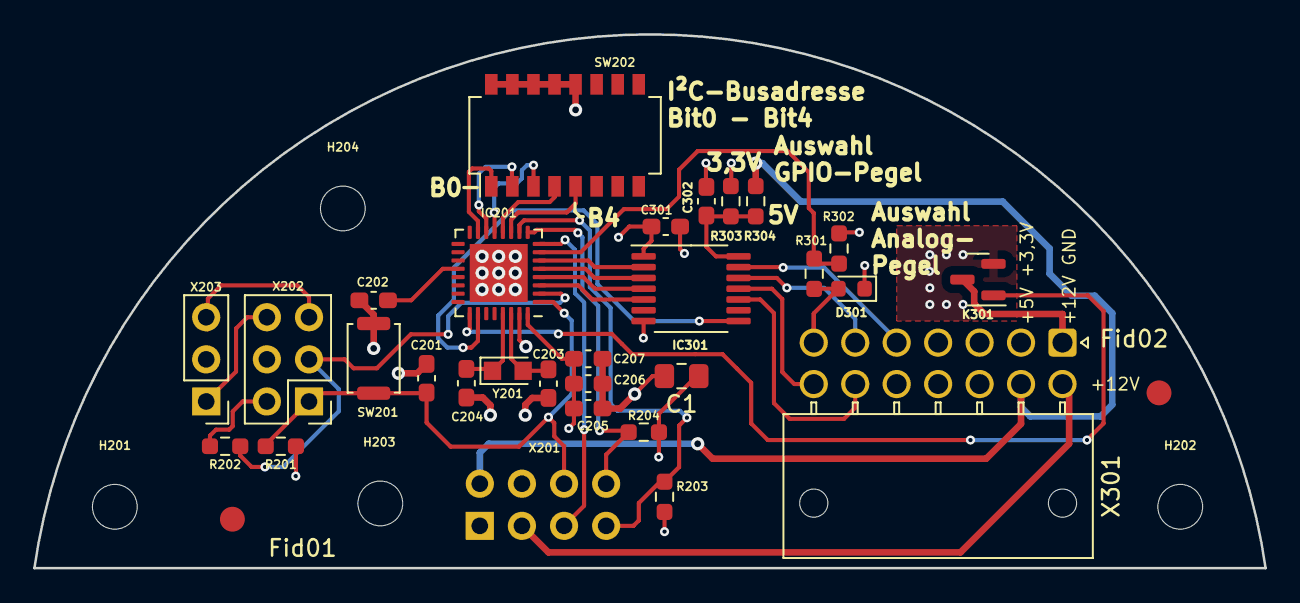
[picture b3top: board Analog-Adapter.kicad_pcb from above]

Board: 4 copper layers, 74.2 x 32.2 mm, 35 parts (1 on the bottom side), 34 nets.

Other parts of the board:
Fid01, Fid02: Fiducial_1.5mm_Mask4.5mm

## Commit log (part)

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2025-09-17 Update issue templates
2025-10-01 proposed solution
    Changed handling of return from influxDB so that list is covered. Needs to be tested deeper. Parameter handling is only a quick fix.
    Also changed the structure so that code should be better maintainable. Needs approval.
    Deleted old pycache and IntelliJ-IDEAS dir.
    Cleaned up recent_deployments.json
2025-10-16 Improve README with updated links for hardware details
    Updated links in the README for schematics and CAD files related to hardware components.
    Added GTIN for USB-C-Plug
2025-10-16 Update BOM.xlsx
    Added GTIN and Link for USB-C-Connector
2025-11-04 Update BOM.xlsx
    Korrektur der Position 16 "Gegenmutter" für den Conductivity Sensor
2025-11-10 Increase antenna size
2025-11-10 is not required
2025-11-10 re-sorted but no adjustments
2025-11-10 Add slot for better grip when tightening screws
2025-11-10 name adjusted to V02
2025-11-10 end_cap_drillings_sensors updated
2025-11-10 name adjusted
2025-11-10 main_unit_MCI updated to V0.5
2025-11-10 main_unit_MCU updated to V0.4
2025-11-10 Added to folder
2025-11-10 I²C-Interfaceboard V0.3
2025-11-10 RS232-Interfaceboard V0.2
2025-11-10 RS485-Interfaceboard V0.2
2025-11-10 UART-Interfaceboard V0.3
2025-11-10 Analog-Interfaceboard V0.1
2025-11-10 Analog-Interfaceboard V0.2
2025-11-11 Analog sensor adapted to 12-bit resolution, Added whether the sensor requires an external parameter
2025-11-14 update to V0.86
    - Multi-client access control: Request to Node-RED to check whether the communication interface is currently busy. Multiple clients can issue requests, but only one is granted exclusive access at a t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
    - The logger will be able to automatically connect to the Wi-Fi network where the last successful login took place. This removes the need to manually sort the entries in the JSON list in the correct 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
    If the most recently successful Wi-Fi connection cannot be established, the Wi-Fi networks stored in the JSON list are tried one after another. As soon as a connection is successful, it is set as the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
    - When the battery is being
2025-11-14 Backup
2025-11-14 old new now nodered_all_flows_20251114.json
2025-11-14 Create nodered_all_flows_20251114.json
    - Multi-client access control: Request to Node-RED to check whether the communication interface is currently busy. Multiple clients can issue requests, but only one is granted exclusive access at a t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
2025-11-17 update media folder
2025-11-17 FW_V0.06
2025-11-18 Update CALIB_FILE
    copied calib_coeff.json to the correct folder, so it is now also displayed correctly when using cg calib_coeff.json
2025-11-18 back to v0.82
2025-11-26 Main_Unit Update
2025-11-27 Node-RED upadte
    - Node-RED Multi-client access control
    - Firmware update switch (30 min) FW-Gate
2025-12-02 Update nodered_all_flows_20251127.json
    waiting time corrected, from 2 to 10 seconds
2025-12-08 update to V0.86
    update to V0.86
    - Multi-client access control: Request to Node-RED to check whether the communication interface is currently busy. Multiple clients can issue requests, but only one is granted exclusive access at a t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
    - The logger will be able to automatically connect to the Wi-Fi network where the last successful login took place. This removes the need to manually sort the entries in the JSON list in the correct 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
    If the most recently successful Wi-Fi connection cannot be established, the Wi-Fi networks stored in the JSON list are tried one after another. As soon as a connection is successful, it is set as the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
    - When t
2025-12-09 Beta FW V0.01
2025-12-09 Beta Firmware update available
2025-12-10 FW 0.01
2025-12-10 Beta FW 0.01
2025-12-10 Update Beta V0.02
    - The LED-Event “Logger detects begin of deployment” has been set to 60 seconds, as specified.
    - Measurement data transmission and log data transmission now have the LED-Event “Logger busy (background process)”.
2025-12-15 Update Beta V0.03
    - DeepSleep has been changed to LightSleep in both the main loop and the sensor measurement loop.
    - Wet sensor (sensor measurement) is now performed once per period.
    - configUpdate and statusUpload now have the LED-Event “Logger busy (background process)”.
2026-01-09 FW 0.07
    - fix: suggestion to fix misinterpreting the first header byte as command, because in SD-Card-Service the first 10 bytes are always header
    - The packet size was reduced from 512 to 180 bytes.
    - “Upload All Data” can be executed via the app (OSBK v1.19.2). However, the query logic in the app is not correct. Correct procedure:
    query the “All Count” once using 0x00,
    then retrieve the measurement values for indices 0–59 … using 0x02.
    - “Upload New Data Only” is currently still faulty in the app. The query logic should be as follows:
2026-01-12 FW 0.08
    - config folder will be created if it does not already exist
    - Fix: datM.csv no longer overwritten
2026-01-13 LED.h an .cpp changed to LedManager
2026-01-13 .clang-format update
2026-01-13 the compiler is now running with C++17 by default
2026-01-15 Update Beta V0.05
    - BMS cleaned up
    - generalError monitoring
    - SD card error monitoring added
    - TODO added
2026-01-16 Update Beta V0.06
    - fix: configUpdate
    - fix: prio generalError();
    - fix: prio reed connection
    - fix: SD card error monitoring
2026-01-19 Update Beta V0.07
    - Done: Made the log level (logging/debugging) configurable via a config parameter without requiring recompilation.
    - Fix: holdOnReedInputPressed — the logger ID was missing in some MQTT error outputs.
2026-01-30 fix(ble): the data upload wasn't working correctly.
    - config service max packet-payload size and smaller packets not padded
    - json format of measurements
    - indices for getting new measurements
2026-01-30 FW 0.09
2026-03-02 Update Interfaceboard Programming Guide
2026-03-02 Update Interfaceboard
    - Pressure sensor (Keller PAA-20D No.: 222022.0129): The interface board basically receives an offset correction in mbar, adjustable via the configuration.
    - O2 (PyroScience PICO-O2-SUB): The interface board output is set to partial pressure (instead of concentration).
2026-03-03 Create sensorIntegration.md
    create new md-file for detail description of sensor integration and calibratin
2026-03-03 Update sensorIntegration.md
    first thoughts about usage and calibration process
2026-03-27 Handle for Rope added
    Added CAD-Files for a fixation to handle the logger with a rope.
    The Assembly has all necessary files. Fixation Rings need to be printed or manufactured in a way that doesn't soak water.
2026-03-31 Reduce the waiting time in water from 60 to 30 seconds (Logger detects begin of deployment)
    ledSignalLoggerDetectsBeginOfDeployment = 30000;
2026-04-15 Update MQTTManager.cpp
    MQTT transmission of measurement data is now being logged
2026-04-15 Update loggerConfig.cpp
    ledColorConfig = 241;
2026-06-09 Update pyroPicoO2.cpp
    O2 adapter board: return µmol/l as processed value and partial pressure in mbar as raw value
2026-06-09 O2 adapter board
    O2 adapter board: return µmol/l as processed value and partial pressure in mbar as raw value
2026-06-17 fix data transfer to json (NaN not valid)
    In some cases NaN was returned to stdout, wich is not valid for the JSON Parsing
    Implement a fix to write None/null instead of NaN
2026-06-24 Fixed blink-code logic and revised status handling.
    - Added status as a bitmask
    - Adjusted blink pause between signals
    - Fixed incorrect blink codes, as the blink pattern was interrupted by Deep Sleep
    - Added blink code for “Skip Sensor”
